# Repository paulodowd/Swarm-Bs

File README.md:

# Swarm-Bs (work in progress)

## Features

- Can be considered a general purpose I2C extension board to provide local infra-red (IR) communication.
- Can also be used stand-alone (example code to come).
- IR Serial transmission at 4800 Baud.
- Transmit/receive upto 28 bytes (currently, extensible).
- Range can be reduced/set with a trimmer potentiometer.
- Message corruption detection implemented with a CRC checksum.
- Designed to conveniently fit to an expansion header of the Pololu 3Pi+ mobile robot.

## Summary

This board is a revised version of the 3Pi_IRComm board. Rather than updating the 3Pi_IRComm repository, it seemed like this board was different enough to have it's own - this way the simpler 3Pi_IRComm board design can persist.  However, this board can be taken as a better design, and unwanted components simply left unpopulated.  The fabrication cost of the PCB is essentially the same.

The board has been revised to include more functionality, especially for human interaction.  The board is intended to now be suitable for both the Pololu 3Pi+ robot and to fit against a wall mounted display.  

Significant changes include:
- It uses an Arduino Nano (rather than an Arduino Pro Mini).
- includes 1 Light Dependent Resistor (LDR).
- includes 3 Potentiometers.
- includes 1 Button.
- includes 1 RGB LED.
- includes a Polarity protection diode.
- includes some necessary resistors.

The Arduino Nano has been used (instead of the pro mini) because it has a built-in USB connector and so is more readily programmable.  This decision was made because these boards may be used as stand-alone devices in classroom workshops - therefore, the firmware isn't necessarily so fixed.  

## Important Considerations

## Bill of Materials (BOM)

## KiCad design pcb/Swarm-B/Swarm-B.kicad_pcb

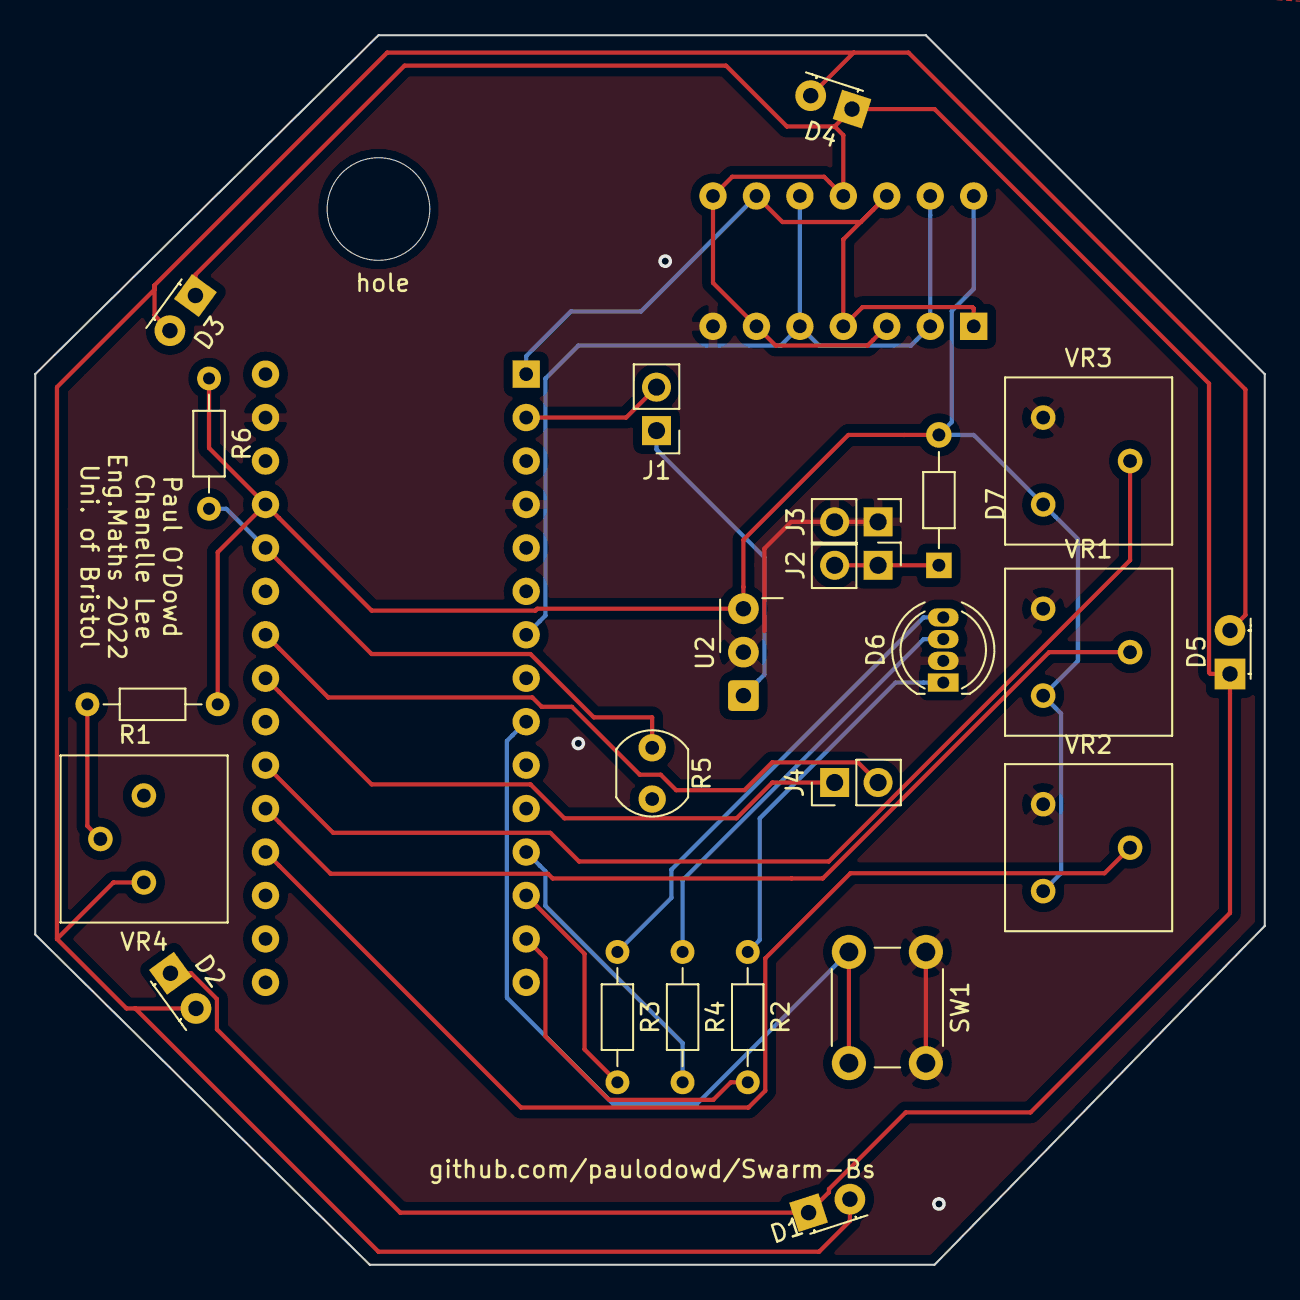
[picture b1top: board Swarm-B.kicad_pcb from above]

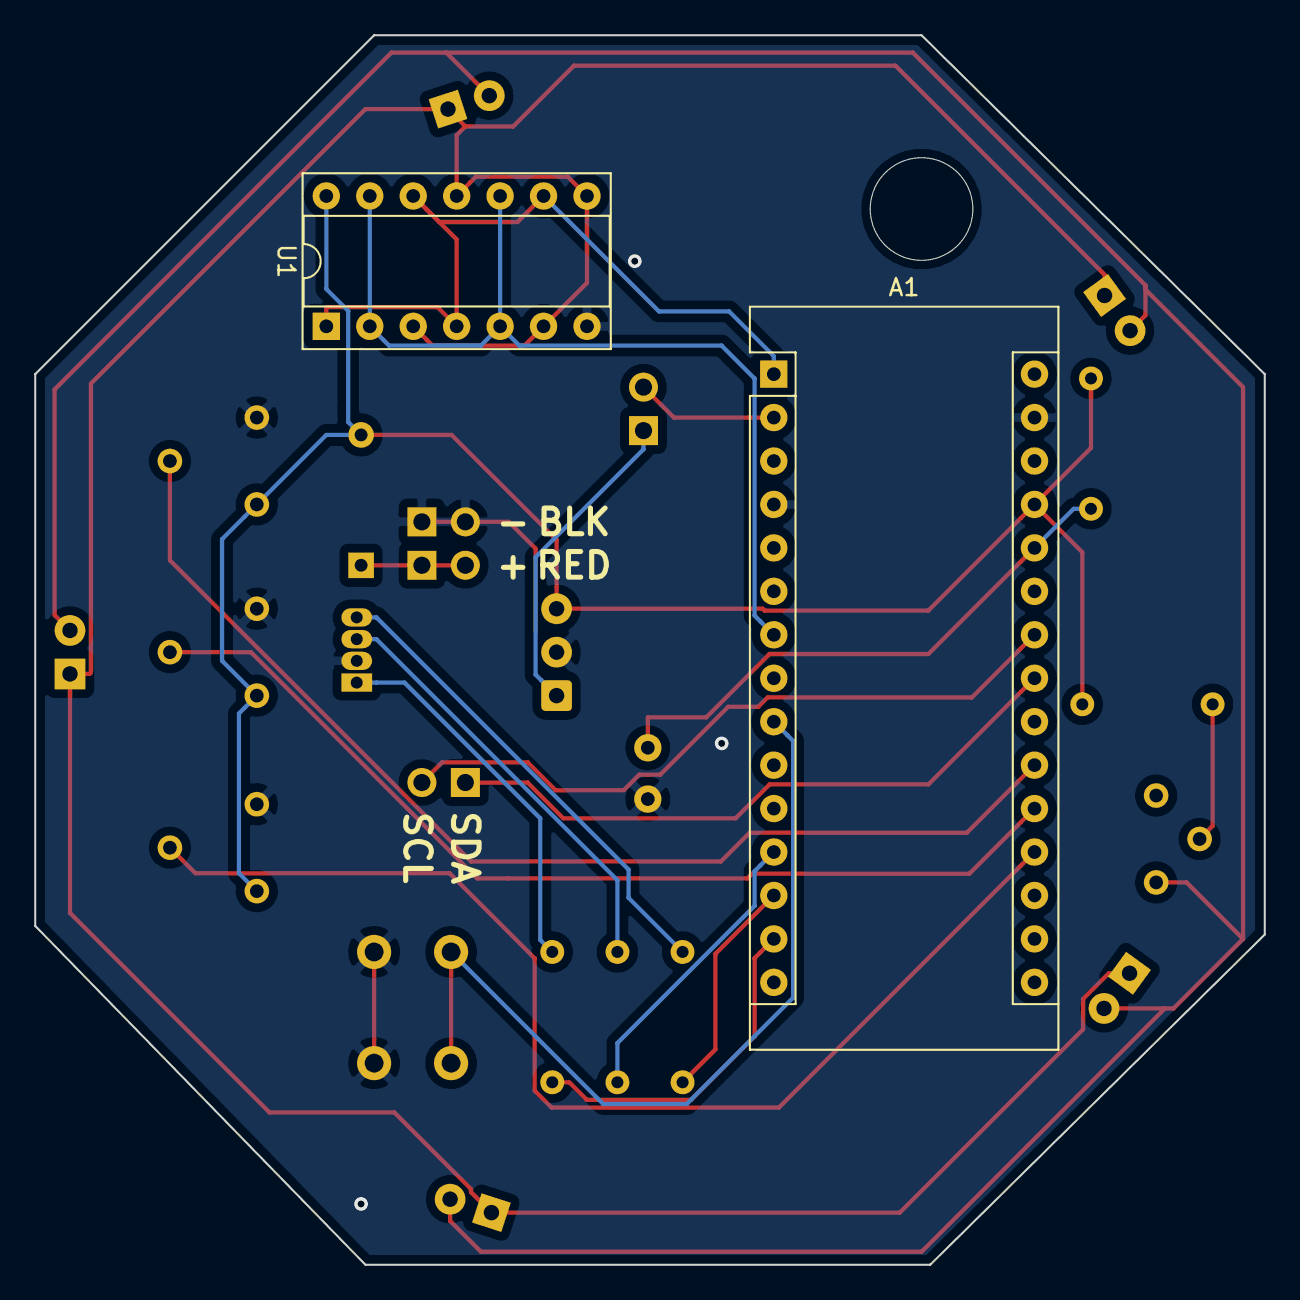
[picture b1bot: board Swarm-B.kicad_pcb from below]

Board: 2 copper layers, 71.9 x 71.9 mm, 26 parts (2 on the bottom side), 23 nets.

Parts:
A1: Arduino_Nano_v3.x; Arduino_Nano
D1, D2, D3, D4, D5: IR_LED; LED_D3.0mm_Horizontal_O1.27mm_Z2.0mm
D6: RGB; LED_D5.0mm-4_RGB
D7: 1N5819; D_DO-34_SOD68_P7.62mm_Horizontal
J1: RX_Break; PinHeader_1x02_P2.54mm_Vertical
J2: 5v_3Pi; PinHeader_1x02_P2.54mm_Vertical
J3: GND_3Pi; PinHeader_1x02_P2.54mm_Vertical
J4: I2C_3Pi; PinHeader_1x02_P2.54mm_Vertical
R1: 15R_IRLED; R_Axial_DIN0204_L3.6mm_D1.6mm_P7.62mm_Horizontal
R2: 155R_R; R_Axial_DIN0204_L3.6mm_D1.6mm_P7.62mm_Horizontal
R3: 90R_G; R_Axial_DIN0204_L3.6mm_D1.6mm_P7.62mm_Horizontal
R4: 85R_B; R_Axial_DIN0204_L3.6mm_D1.6mm_P7.62mm_Horizontal
R5: LDR; R_LDR_5.0x4.1mm_P3mm_Vertical
R6: 10K_LDR; R_Axial_DIN0204_L3.6mm_D1.6mm_P7.62mm_Horizontal
SW1: Bttn; SW_PUSH_6mm
U1: 74LS32; DIP-14_W7.62mm_Socket
U2: TSDP34138; Vishay_MOLD-3Pin
VR1: 10K_Pot_B; Potentiometer_Bourns_3386F_Vertical
VR2: 10K_Pot_A; Potentiometer_Bourns_3386F_Vertical
VR3: 10K_Pot_C; Potentiometer_Bourns_3386F_Vertical
VR4: 1K_Pot_IRLED; Potentiometer_Bourns_3386P_Vertical
hole: hole; MountingHole_6mm

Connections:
+5V: A1.27, D7.2, R1.1, R6.1, U1.14, U2.3, VR1.1, VR2.1, VR3.1
GND: A1.4, A1.29, D6.2, J3.1, J3.2, R5.2, SW1.1, U1.7, U2.2, VR1.3, VR2.3, VR3.3
unnamed: A1.1, U1.1, U1.4, U1.9, U1.12
unnamed: A1.2, J1.2
unnamed: A1.7, U1.2, U1.5, U1.10, U1.13
unnamed: A1.9, SW1.2
unnamed: A1.12, R4.2
unnamed: A1.13, R3.2
unnamed: A1.14, R2.2
unnamed: A1.19, VR2.2
unnamed: A1.20, VR1.2
unnamed: A1.21, VR3.2
unnamed: A1.23, J4.1
unnamed: A1.24, J4.2
unnamed: A1.26, R5.1, R6.2
unnamed: D1.1, D2.1, D3.1, D4.1, D5.1, U1.3, U1.6, U1.8, U1.11
unnamed: D1.2, D2.2, D3.2, D4.2, D5.2, VR4.3
unnamed: D6.1, R2.1
unnamed: D6.3, R4.1
unnamed: D6.4, R3.1
unnamed: D7.1, J2.1, J2.2
unnamed: J1.1, U2.1
unnamed: R1.2, VR4.2

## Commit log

2022-03-16 added sda and scl labels to pcb
2022-03-17 update to readme
2022-06-01 altered pcb to house ICs on the underside
2022-06-09 added arduino nano firmware
2022-06-09 minor bug fix
2022-06-21 removed debug statement
